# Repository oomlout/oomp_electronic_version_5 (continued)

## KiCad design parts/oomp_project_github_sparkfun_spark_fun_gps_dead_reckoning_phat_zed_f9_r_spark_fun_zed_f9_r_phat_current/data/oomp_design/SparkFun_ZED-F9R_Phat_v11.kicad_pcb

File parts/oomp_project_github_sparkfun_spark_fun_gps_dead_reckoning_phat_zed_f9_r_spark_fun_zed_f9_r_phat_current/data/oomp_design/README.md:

# OOMP KiCad design copy

Open `SparkFun_ZED-F9R_Phat_v11.kicad_pro` (or the `.kicad_pcb` / `.kicad_sch`) in KiCad. Local OOMP libraries are under `libraries/`. Original inputs are preserved in [../original/](../original/).

Only verified unchanged installed KiCad defaults were renamed. Modified, custom, unmatched and unavailable items remain unchanged. Soldering variants are never swapped during conversion. Existing pad coordinates, nets and UUIDs are preserved.

See [conversion_report.yaml](conversion_report.yaml) for every conversion and skip. Copy this directory before editing; regeneration refuses to overwrite edited design files.

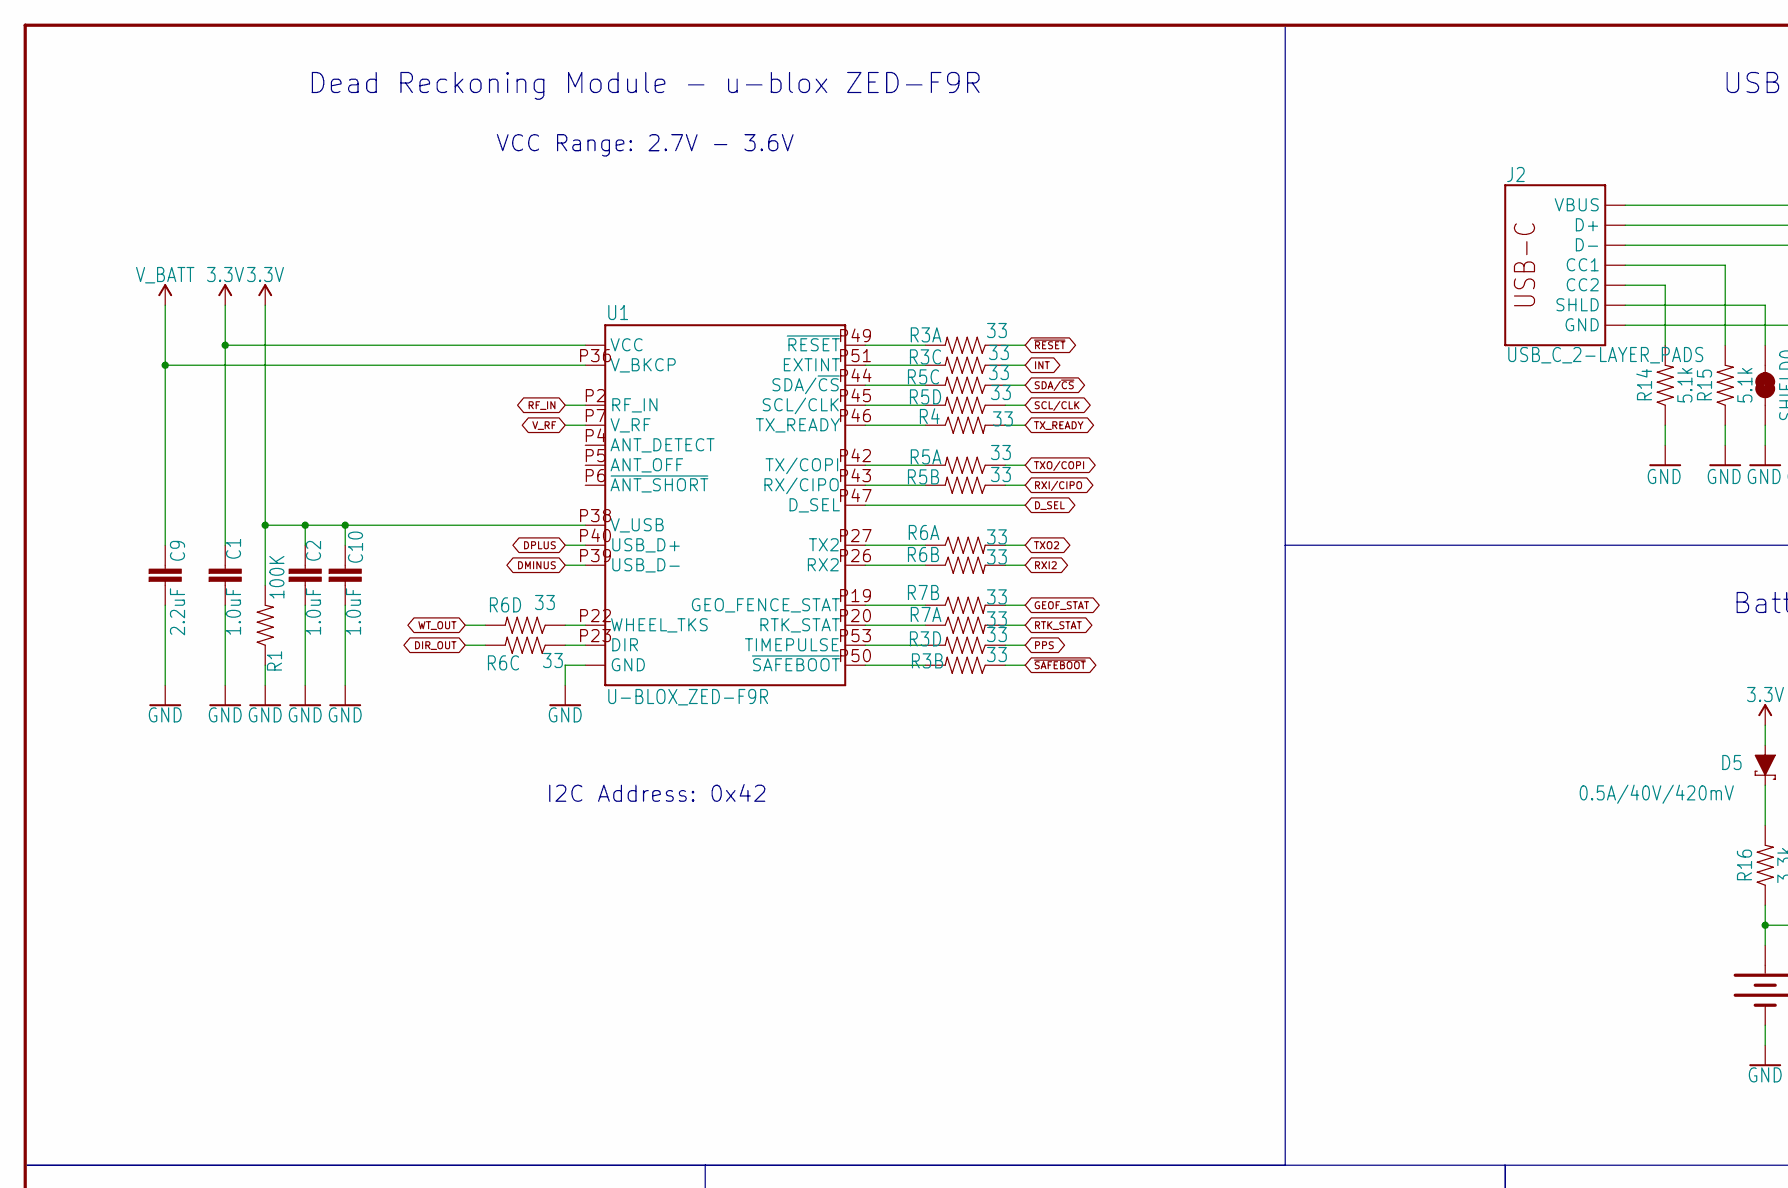
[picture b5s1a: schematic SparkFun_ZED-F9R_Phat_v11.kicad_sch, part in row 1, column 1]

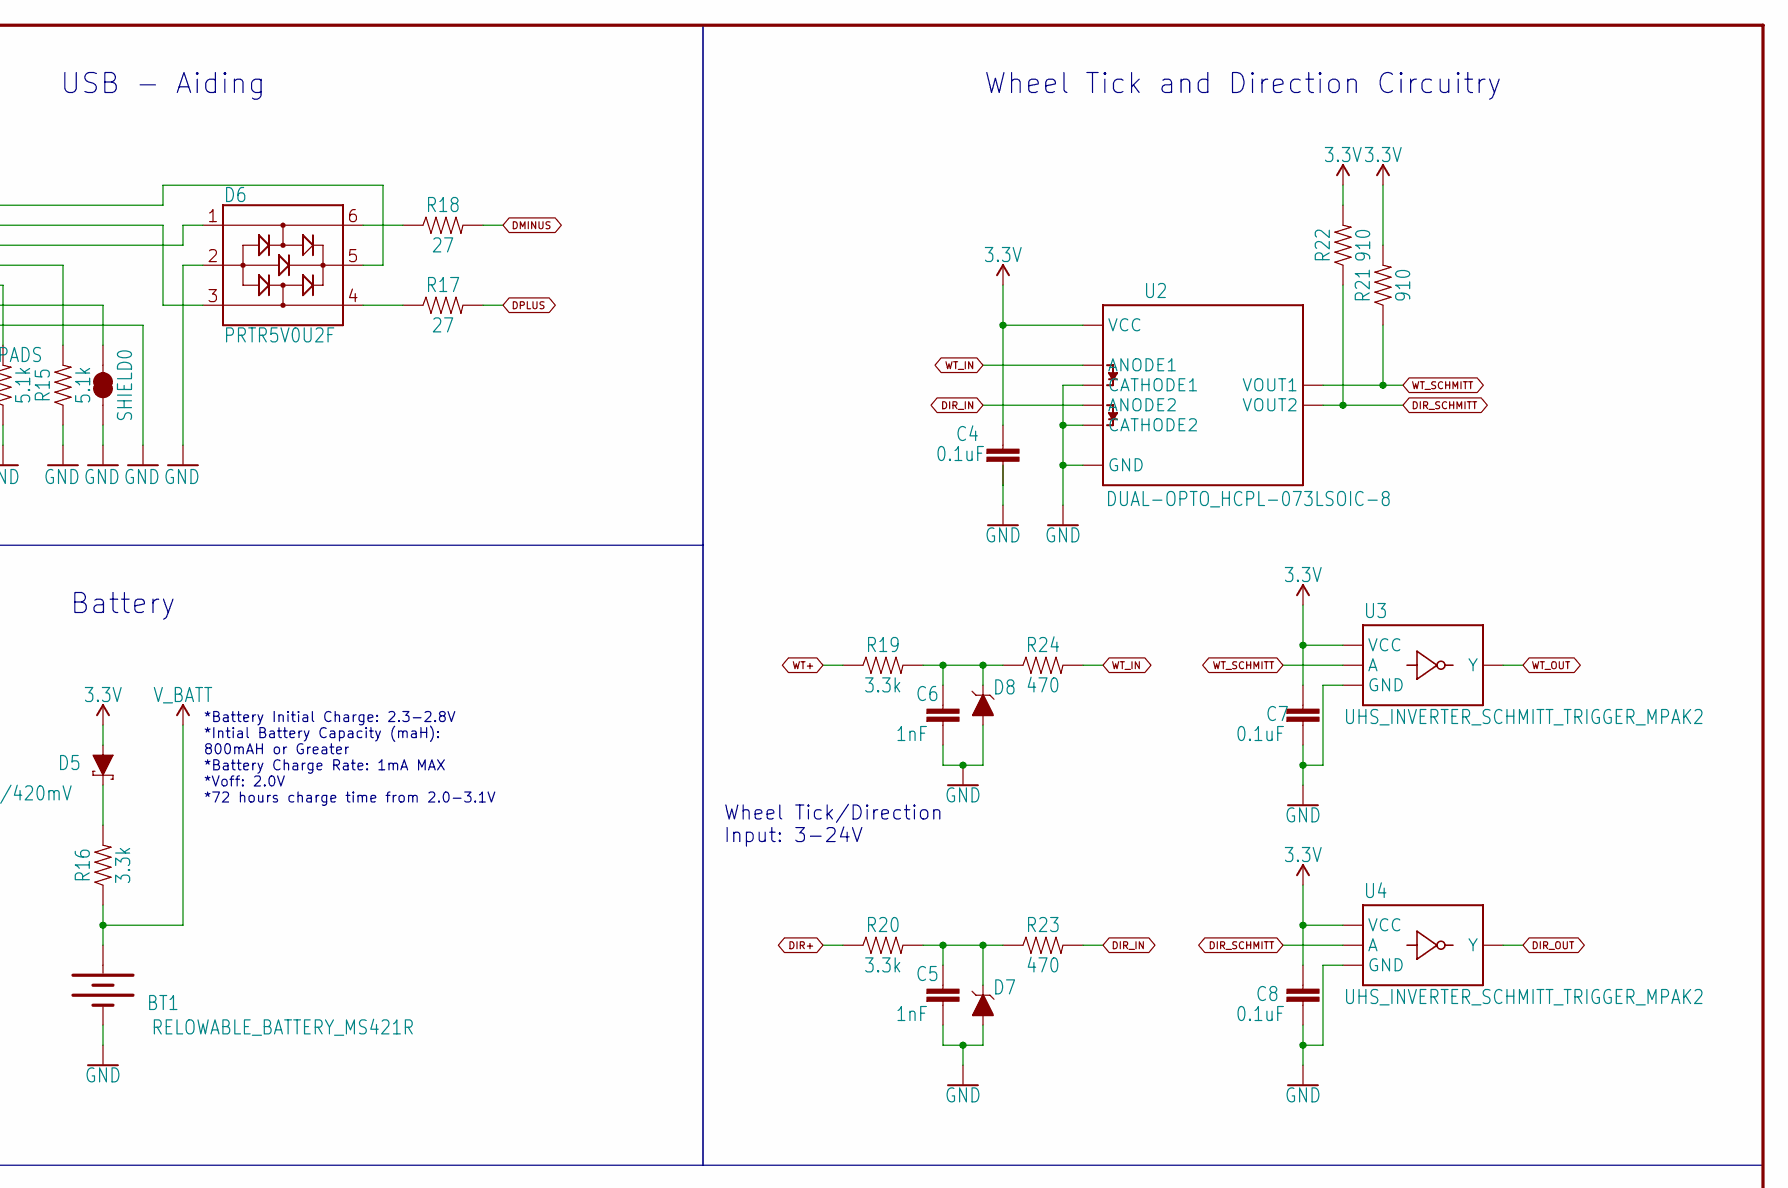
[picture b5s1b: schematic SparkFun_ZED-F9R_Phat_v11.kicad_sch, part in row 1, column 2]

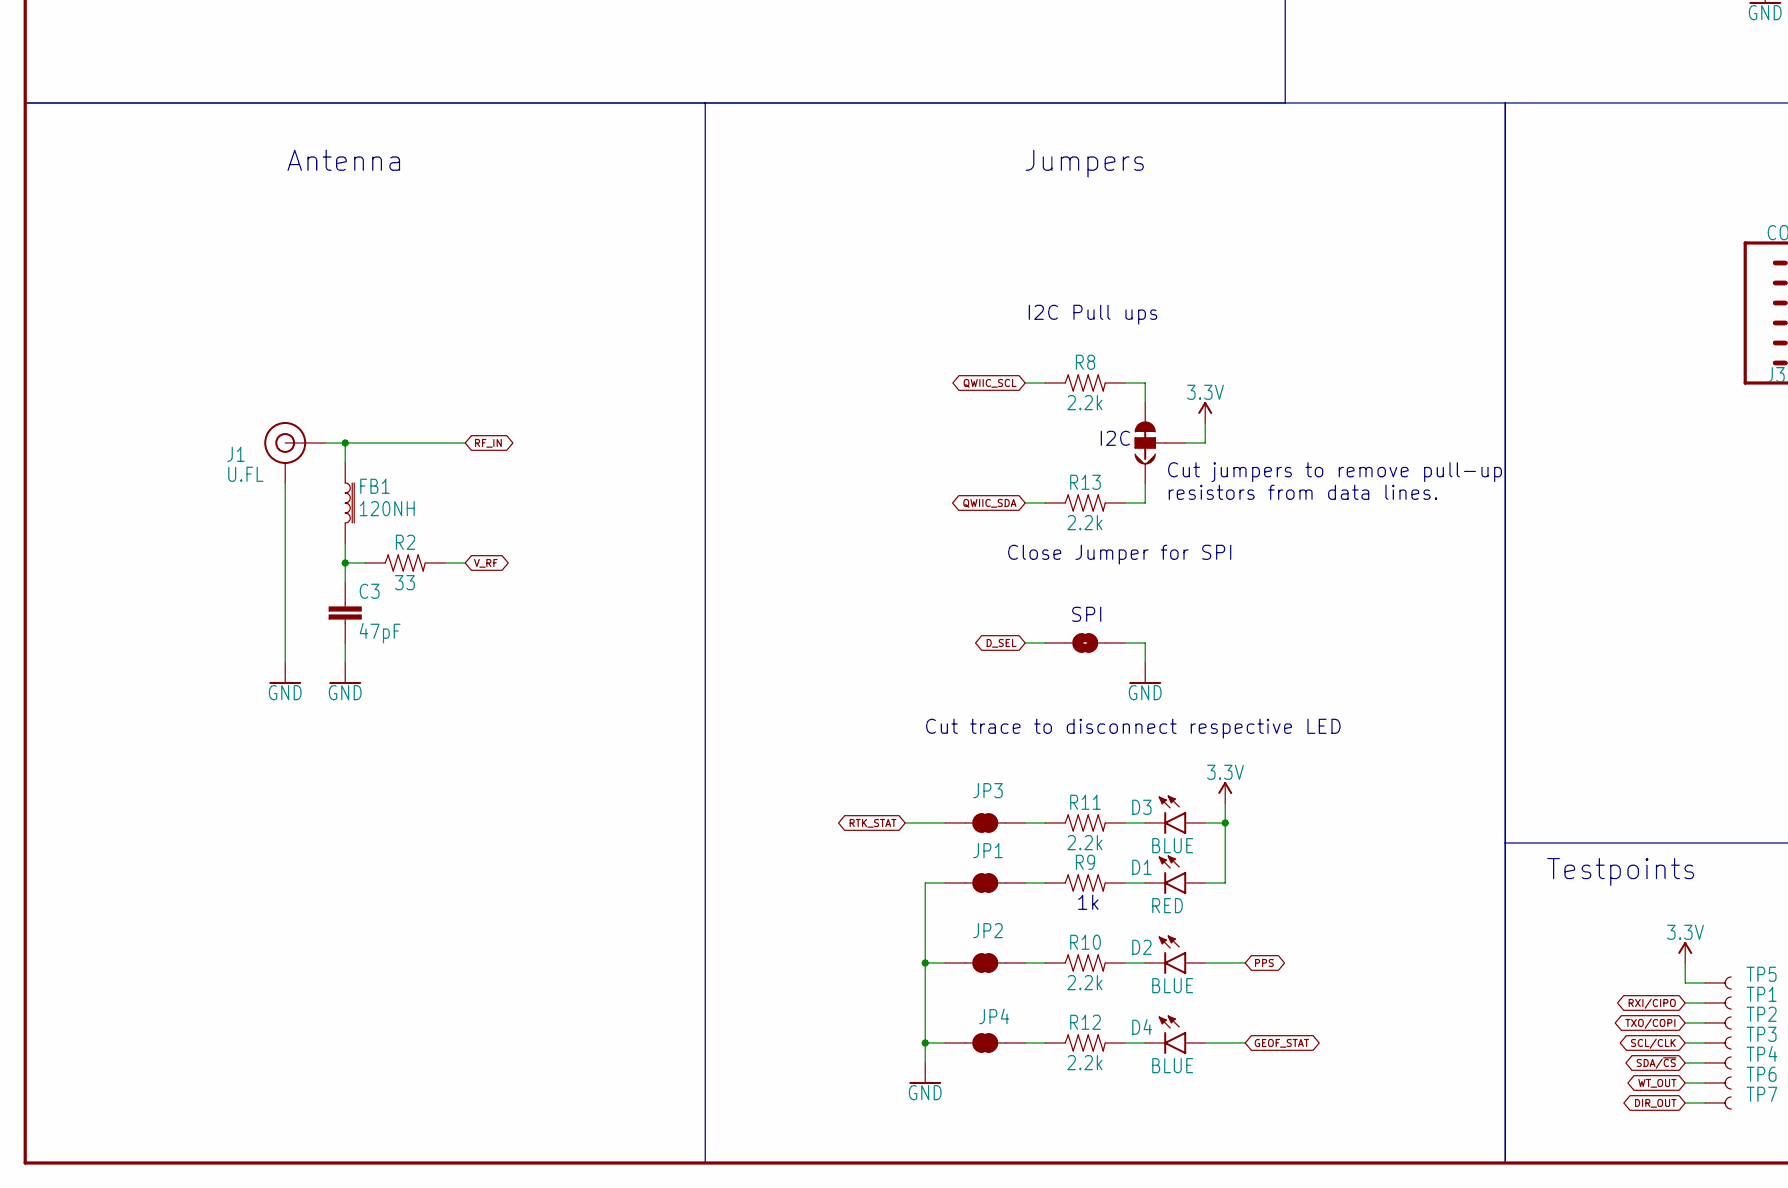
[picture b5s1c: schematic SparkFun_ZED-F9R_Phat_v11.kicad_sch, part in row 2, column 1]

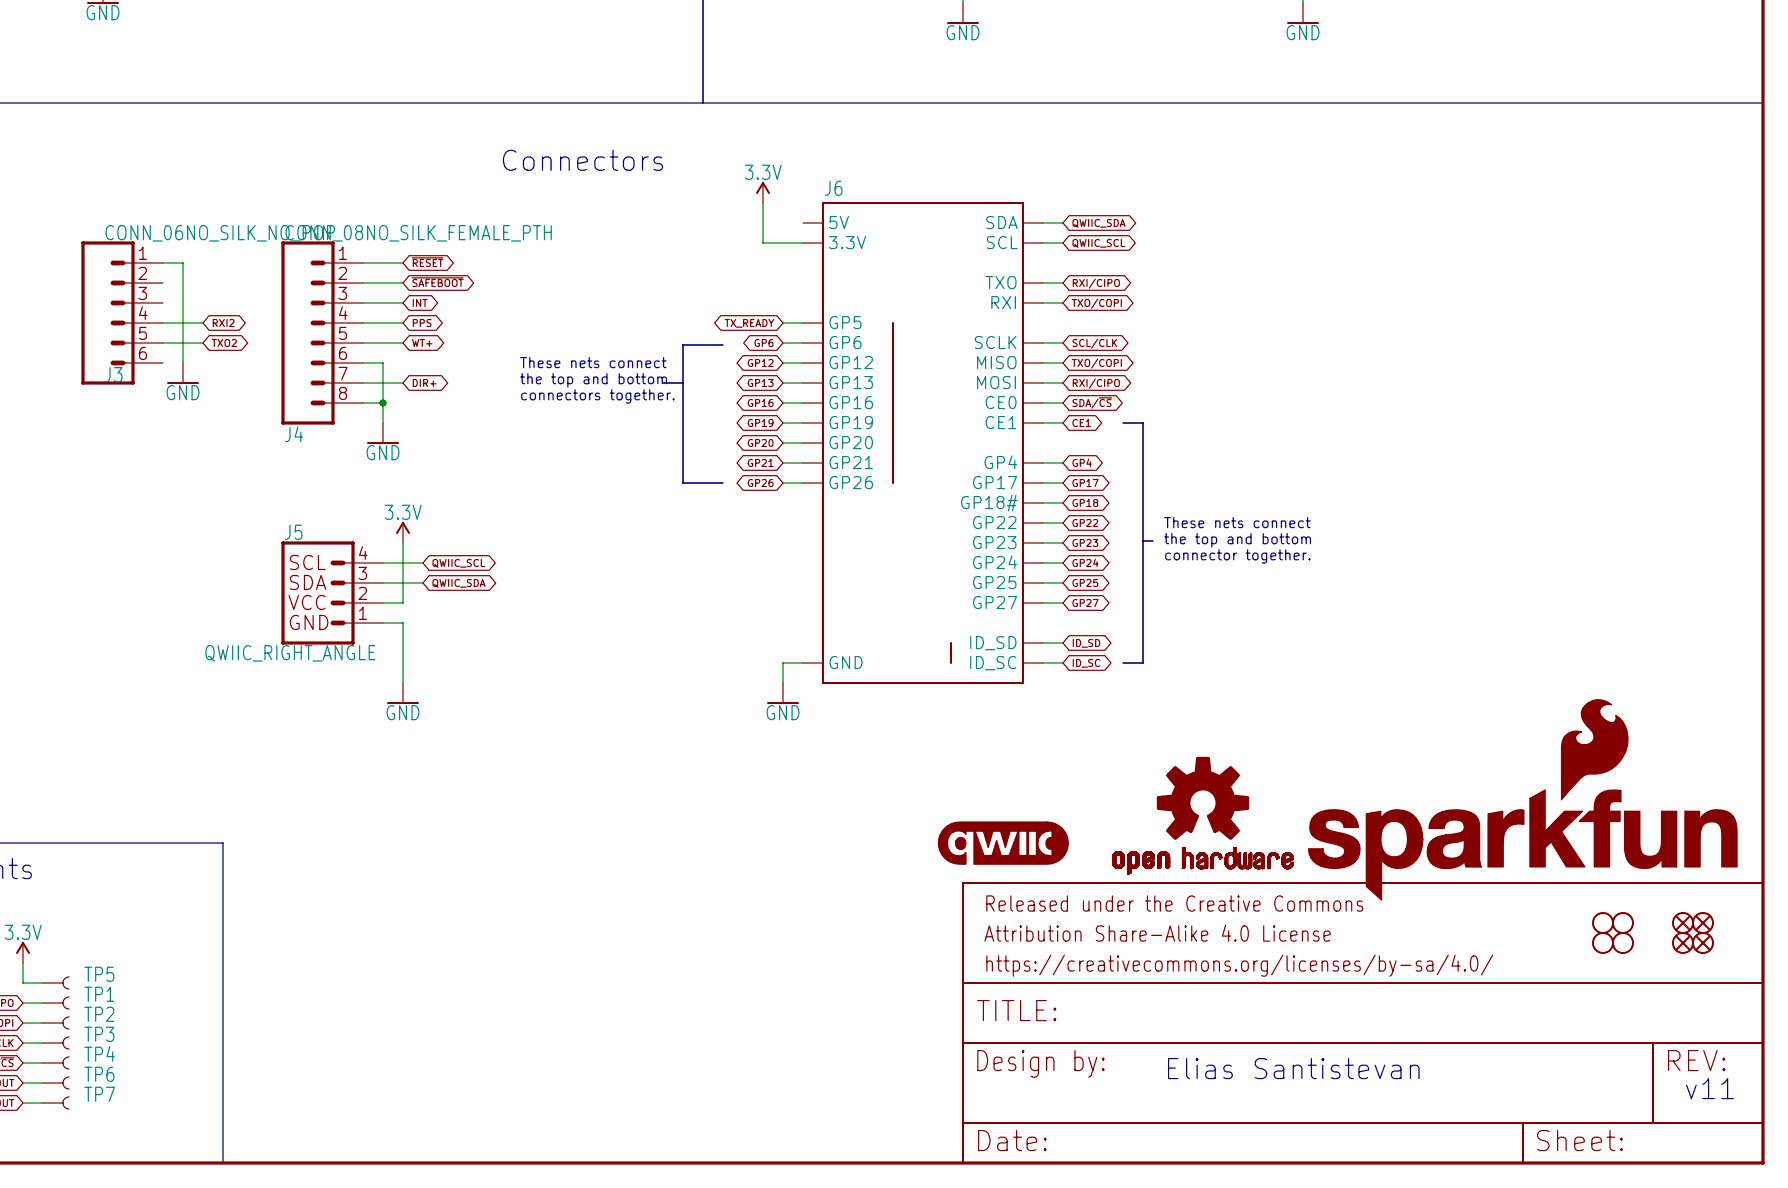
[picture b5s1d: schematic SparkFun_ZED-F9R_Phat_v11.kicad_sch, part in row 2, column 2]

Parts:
BT1: RELOWABLE_BATTERY_MS421R; MS421R_IV03E
C1, C2, C10: 1.0uF; 0402
C3: 47pF; 0402
C4, C7, C8: 0.1uF; 0402
C5, C6: 1nF; 0402
C9: 2.2uF; 0402-TIGHT
D1: RED; LED-0603
D2, D3, D4: BLUE; LED-0603
D5: 0.5A/40V/420mV; SOD-323
D6: PRTR5V0U2F; SOT886
D7, D8: 15V; SOT23-3
FB1: 120NH; 0402_MURATA
FD1, FD2, FD3, FD4: FIDUCIALUFIDUCIAL; FIDUCIAL-MICRO
FRAME1: FRAME-LEDGER; CREATIVE_COMMONS
H1, H2, H3, H4: STAND-OFFTIGHT; STAND-OFF-TIGHT
J1: U.FL
J2: USB_C_2-LAYER_PADS; USB-C-16P-2LAYER-PADS
J3: CONN_06NO_SILK_NO_POP; 1X06_NO_SILK
J4: CONN_08NO_SILK_FEMALE_PTH; 1X08_NO_SILK
J5: QWIIC_RIGHT_ANGLE; JST04_1MM_RA
J6: RASPBERRYPI-40-PIN-GPIO_SMD_STACK_NOHOLES_NOREF; RASPBERRY_PI_HAT_40_PIN_SMD_STACKABLE_NOHOLES_NOREF
JP1, JP2, JP3, JP4: JUMPER-SMT_2_NC_TRACE_SILK; SMT-JUMPER_2_NC_TRACE_SILK
JP5: JUMPER-SMT_2_NO_SILK; SMT-JUMPER_2_NO_SILK
JP6: JUMPER-SMT_3_2-NC_TRACE_SILK; SMT-JUMPER_3_2-NC_TRACE_SILK
LOGO1: QWIIC_LOGO_5MM; QWIIC_5MM
LOGO2: OSHW-LOGOM; OSHW-LOGO-M
LOGO3: SFE_LOGO_NAME_FLAME.2_INCH; SFE_LOGO_NAME_FLAME_.2
R1: 100K; 0402
R2, R4: 33; 0603
R3, R5, R6, R7: 33; 1206_RA
R8, R10, R11, R12, R13: 2.2k; 0603
R9: 1k; 0603
R14, R15: 5.1k; 0402
R16, R19, R20: 3.3k; 0603
R17, R18: 27; 0603
R21, R22: 910; 0603
R23, R24: 470; 0603
SHIELD0: JUMPER-SMT_2_NC_TRACE_SILK; SMT-JUMPER_2_NC_TRACE_SILK
TP1, TP2, TP3, TP4, TP5, TP6, TP7: TEST-POINT3X4; PAD.03X.04
U1: U-BLOX_ZED-F9R; UBLOX_ZED_F9R
U2: DUAL-OPTO_HCPL-073LSOIC-8; SO08
U3, U4: UHS_INVERTER_SCHMITT_TRIGGER_MPAK2; SIP6_MICROPAK2

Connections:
3.3V: C1.1, C2.1, C4.1, C7.1, C8.1, C10.1, D1.A, D3.A, D5.A, J5.2, J6.1 (3.3V), J6.1B (3.3V), J6.17 (3.3V), J6.17B (3.3V), JP6.2, R1.2, R21.2, R22.2, TP5.P$1, U1.P33 (VCC), U1.P34 (VCC), U1.P38 (V_USB), U2.8 (VCC), U3.P6 (VCC), U4.P6 (VCC)
5V: J6.2 (5V), J6.2B (5V), J6.4 (5V), J6.4B (5V)
CE1: J6.26 (CE1), J6.26B (CE1)
DIR+: J4.7, R20.1
DIR_IN: R23.2, U2.4 (ANODE2)
DIR_OUT: R6.P6 (2), TP7.P$1, U4.P4 (Y)
DIR_SCHMITT: R22.1, U2.6 (VOUT2), U4.P2 (A)
DMINUS: R18.2, U1.P39 (USB_D-)
DPLUS: R17.2, U1.P40 (USB_D+)
D_SEL: JP5.1, U1.P47 (D_SEL)
GEOF_STAT: D4.A, R7.P7 (2)
GND: BT1.-, C1.2, C2.2, C3.2, C4.2, C5.2, C6.2, C7.2, C8.2, C9.2, C10.2, D6.2, D7.1 (A), D8.1 (A), J1.1 (GND), J1.2 (GND), J2.GND, J2.GND2 (GND), J3.1, J4.6, J4.8, J5.1, J6.6 (GND), J6.6B (GND), J6.9 (GND), J6.9B (GND), J6.14 (GND), J6.14B (GND), J6.20 (GND), J6.20B (GND), J6.25 (GND), J6.25B (GND), J6.30 (GND), J6.30B (GND), J6.34 (GND), J6.34B (GND), J6.39 (GND), J6.39B (GND), JP1.1, JP2.1, JP4.1, JP5.2, R1.1, R14.1, R15.1, SHIELD0.1, U1.G1 (GND), U1.G2 (GND), U1.G3 (GND), U1.G4 (GND), U1.G5 (GND), U1.G6 (GND), U1.G7 (GND), U1.G8 (GND), U1.G9 (GND), U1.G10 (GND), U1.G11 (GND), U1.G12 (GND), U1.G13 (GND), U1.G14 (GND), U1.G15 (GND), U1.G16 (GND), U1.G17 (GND), U1.G18 (GND), U1.G19 (GND), U1.G20 (GND), U1.G21 (GND), U1.G22 (GND), U1.G23 (GND), U1.G24 (GND), U1.G25 (GND), U1.G26 (GND), U1.G27 (GND), U1.G28 (GND), U1.G29 (GND), U1.G30 (GND), U1.G31 (GND), U1.G32 (GND), U1.G33 (GND), U1.G34 (GND), U1.G35 (GND), U1.G36 (GND), U1.G37 (GND), U1.G38 (GND), U1.G39 (GND), U1.G40 (GND), U1.G41 (GND), U1.G42 (GND), U1.G43 (GND), U1.G44 (GND), U1.G45 (GND), U1.G46 (GND), U1.G47 (GND), U1.G48 (GND), U1.P1 (GND), U1.P3 (GND), U1.P12 (GND), U1.P14 (GND), U1.P32 (GND), U1.P37 (GND), U1.P41 (GND), U1.P48 (GND), U2.2 (CATHODE1), U2.3 (CATHODE2), U2.5 (GND), U3.P3 (GND), U4.P3 (GND)
GP4: J6.7 (GP4), J6.7B (GP4)
GP6: J6.31 (GP6), J6.31B (GP6)
GP12: J6.32 (GP12), J6.32B (GP12)
GP13: J6.33 (GP13), J6.33B (GP13)
GP16: J6.36 (GP16), J6.36B (GP16)
GP17: J6.11 (GP17), J6.11B (GP17)
GP18: J6.12 (GP18#), J6.12B (GP18#)
GP19: J6.35 (GP19), J6.35B (GP19)
GP20: J6.38 (GP20), J6.38B (GP20)
GP21: J6.40 (GP21), J6.40B (GP21)
GP22: J6.15 (GP22), J6.15B (GP22)
GP23: J6.16 (GP23), J6.16B (GP23)
GP24: J6.18 (GP24), J6.18B (GP24)
GP25: J6.22 (GP25), J6.22B (GP25)
GP26: J6.37 (GP26), J6.37B (GP26)
GP27: J6.13 (GP27), J6.13B (GP27)
ID_SC: J6.28 (ID_SC), J6.28B (ID_SC)
ID_SD: J6.27 (ID_SD), J6.27B (ID_SD)
INT: J4.3, R3.P3 (1)
unnamed: JP6.1, R13.2
unnamed: D5.C, R16.2
unnamed: JP6.3, R8.2
unnamed: D1.C, R9.2
unnamed: C3.1, FB1.P2 (2), R2.1
unnamed: D6.6, R18.1
unnamed: D6.4, R17.1
unnamed: JP1.2, R9.1
unnamed: D6.3, J2.A6 (D+), J2.B6 (D+)
unnamed: D6.5, J2.VBUS1 (VBUS), J2.VBUS2 (VBUS)
unnamed: D6.1, J2.A7 (D-), J2.B7 (D-)
unnamed: J2.B5 (CC2), R14.2
unnamed: R3.P8 (2), U1.P49 (~RESET)
unnamed: R3.P6 (2), U1.P51 (EXTINT)
unnamed: R5.P6 (2), U1.P44 (SDA/~CS)
unnamed: JP4.2, R12.1
unnamed: D4.C, R12.2
unnamed: J2.A5 (CC1), R15.2
unnamed: R5.P5 (2), U1.P45 (SCL/CLK)
unnamed: R4.1, U1.P46 (TX_READY)
unnamed: R5.P8 (2), U1.P42 (TX/COPI)
unnamed: JP3.2, R11.1
unnamed: JP2.2, R10.1
unnamed: D2.C, R10.2
unnamed: D3.C, R11.2
unnamed: R5.P7 (2), U1.P43 (RX/CIPO)
unnamed: C6.1, D8.3 (C), R19.2, R24.1
unnamed: R7.P2 (1), U1.P19 (GEO_FENCE_STAT)
unnamed: R7.P1 (1), U1.P20 (RTK_STAT)
unnamed: R3.P5 (2), U1.P53 (TIMEPULSE)
unnamed: R3.P7 (2), U1.P50 (~SAFEBOOT)
unnamed: R6.P1 (1), U1.P27 (TX2)
unnamed: R6.P2 (1), U1.P26 (RX2)
unnamed: R6.P4 (1), U1.P22 (WHEEL_TKS)
unnamed: R6.P3 (1), U1.P23 (DIR)
unnamed: C5.1, D7.3 (C), R20.2, R23.1
PPS: D2.A, J4.4, R3.P4 (1)
QWIIC_SCL: J5.4, J6.5 (SCL), J6.5B (SCL), R8.1
QWIIC_SDA: J5.3, J6.3 (SDA), J6.3B (SDA), R13.1
RF_IN: FB1.P1 (1), J1.FEED (SIGNAL), U1.P2 (RF_IN)
RTK_STAT: JP3.1, R7.P8 (2)
RXI2: J3.4, R6.P7 (2)
RXI/CIPO: J6.8 (TXO), J6.8B (TXO), J6.19 (MOSI), J6.19B (MOSI), R5.P2 (1), TP1.P$1
SCL/CLK: J6.23 (SCLK), J6.23B (SCLK), R5.P4 (1), TP3.P$1
SDA/~CS: J6.24 (CE0), J6.24B (CE0), R5.P3 (1), TP4.P$1
SHIELD: J2.SHLD1 (SHLD), J2.SHLD2 (SHLD), J2.SHLD3 (SHLD), J2.SHLD4 (SHLD), SHIELD0.2
TXO2: J3.5, R6.P8 (2)
TXO/COPI: J6.10 (RXI), J6.10B (RXI), J6.21 (MISO), J6.21B (MISO), R5.P1 (1), TP2.P$1
TX_READY: J6.29 (GP5), J6.29B (GP5), R4.2
V_BATT: BT1.+, C9.1, R16.1, U1.P36 (V_BKCP)
V_RF: R2.2, U1.P7 (V_RF)
WT+: J4.5, R19.1
WT_IN: R24.2, U2.1 (ANODE1)
WT_OUT: R6.P5 (2), TP6.P$1, U3.P4 (Y)
WT_SCHMITT: R21.1, U2.7 (VOUT1), U3.P2 (A)
~RESET: J4.1, R3.P1 (1)
~SAFEBOOT: J4.2, R3.P2 (1)

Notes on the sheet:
I2C Pull ups
These nets connect the top and bottom connectors together.
These nets connect the top and bottom connector together.
Wheel Tick and Direction Circuitry
Connectors
USB - Aiding
SPI
Close Jumper for SPI
I2C
Antenna
Dead Reckoning Module - u-blox ZED-F9R
Elias Santistevan
v11
I2C Address: 0x42
Wheel Tick/Direction Input: 3-24V
Testpoints
Cut trace to disconnect respective LED
Battery
Cut jumpers to remove pull-up resistors from data lines.
VCC Range: 2.7V - 3.6V
Jumpers
*Battery Initial Charge: 2.3-2.8V *Intial Battery Capacity (maH): 800mAH or Greater *Battery Charge Rate: 1mA MAX *Voff: 2.0V *72 hours charge time from 2.0-3.1V

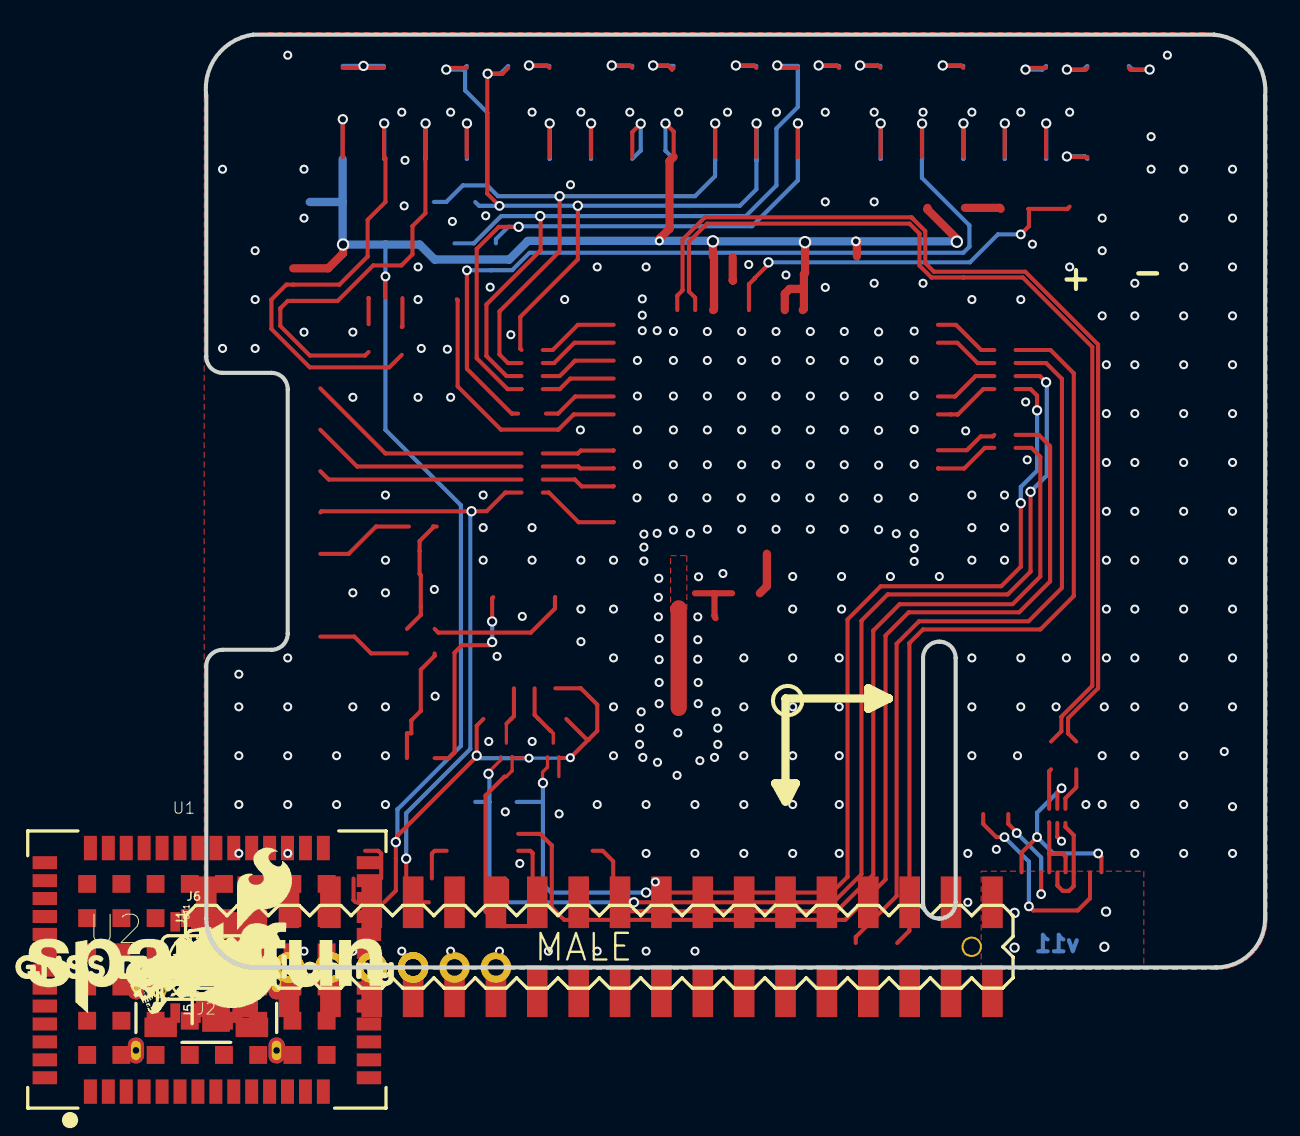
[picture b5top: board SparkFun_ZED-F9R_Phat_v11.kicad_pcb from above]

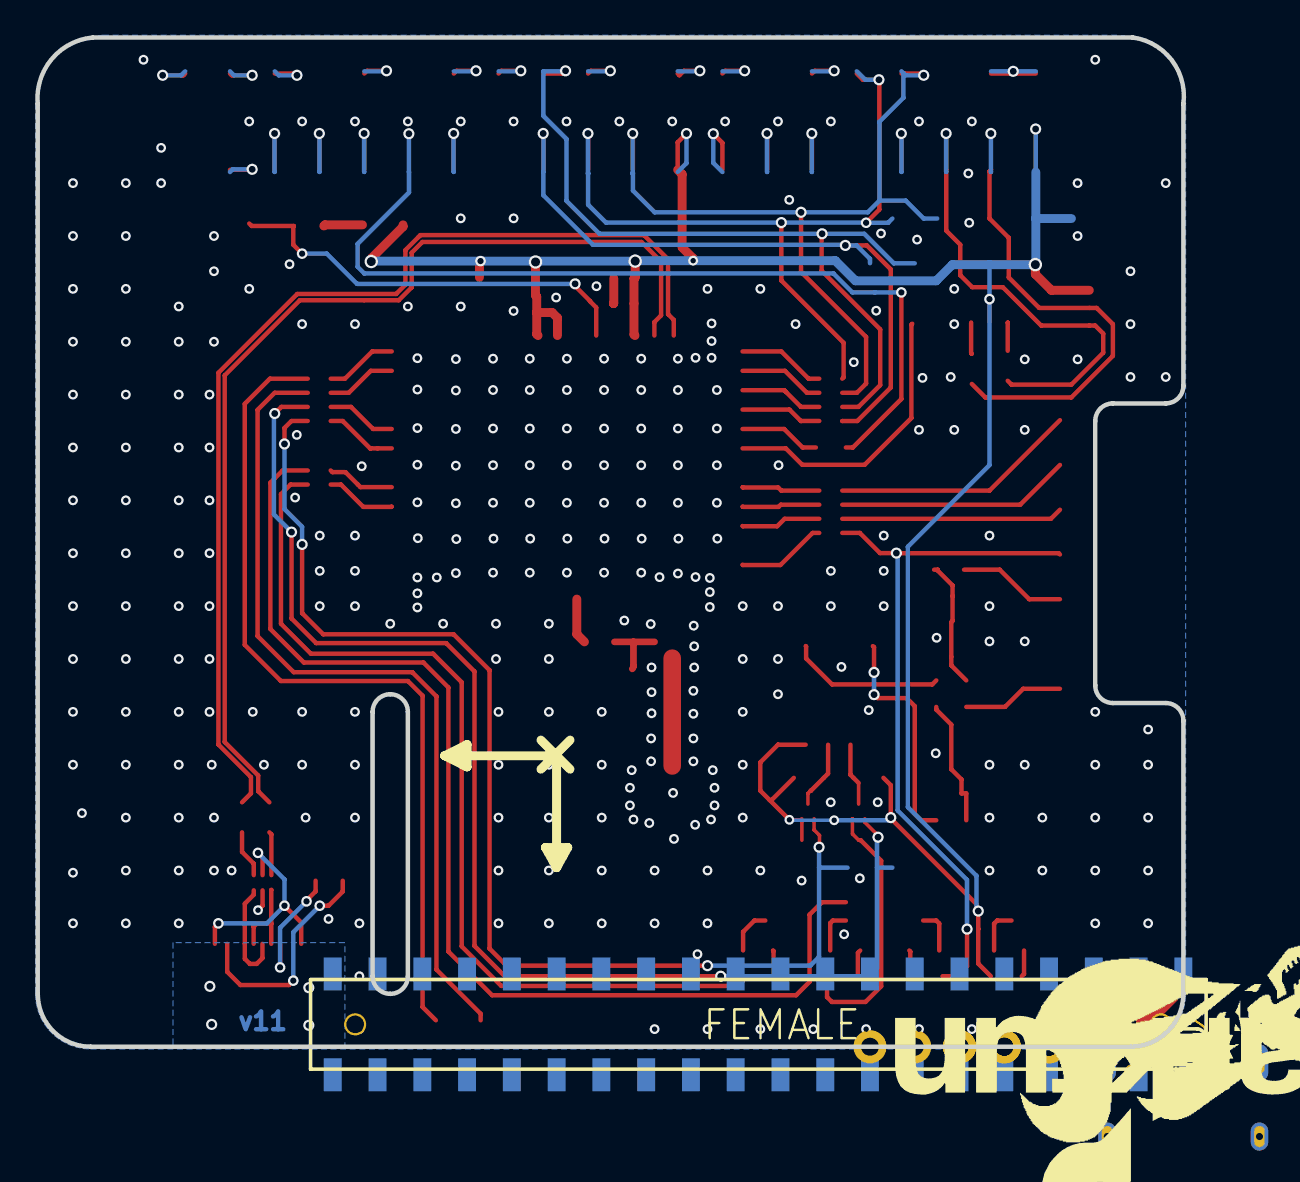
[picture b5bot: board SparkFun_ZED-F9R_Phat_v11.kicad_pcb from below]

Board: 2 copper layers, 65.0 x 57.3 mm, 124 parts (27 on the bottom side), 88 nets.

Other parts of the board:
U$1: ##RST##28
U$2: ##SFBT##30
U$3: PPS9
U$4: PWR7
U$5: GEO11
U$6: #RXI2#34
U$7: #INT#1
U$8: #PPS#3
U$9: SFE_LOGO_NAME_FLAME_.3@1
U$10: #TXO2#235
U$11: #W##2253
U$12: #W##2254
U$13: #D##2249
U$14: GNSS_DEAD_RECKONING25
U$15: #D##2250
U$16: ZED#F9R25
U$17: BLK22
U$18, U$19: #GND#20
U$20: #SPI#4
U$21: L1#L26
U$22: #I2C#5
U$23: RTK13
U$24: GRN23
U$25, U$28: Z20
U$26, U$29: Y19
U$27, U$45: X18
U$31, U$36: DEAD#RECKONING#GPS#BOARD#SILK#FINAL#JPG
U$32: ##RST##27
U$33: ##SFBT##29
U$34: #INT#0
U$35: #PPS#2
U$37: #W##2251
U$38: #W##2252
U$39: #D##2247
U$40: #D##2248
U$41: ANTENNA6
U$42: #TXO2#236
U$43: #RXI2#35
U$44: #SHLD#2258

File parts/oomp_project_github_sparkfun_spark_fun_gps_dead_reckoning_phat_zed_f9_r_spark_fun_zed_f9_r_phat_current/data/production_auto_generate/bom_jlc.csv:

Comment,Designator,Footprint,LCSC Part #
,U$32,SparkFun_ZED-F9R_Phat_v11-import-fps:##RST##27,
,U$1,SparkFun_ZED-F9R_Phat_v11-import-fps:##RST##28,
,U$33,SparkFun_ZED-F9R_Phat_v11-import-fps:##SFBT##29,
,U$2,SparkFun_ZED-F9R_Phat_v11-import-fps:##SFBT##30,
,U$39,SparkFun_ZED-F9R_Phat_v11-import-fps:#D##2247,
,U$40,SparkFun_ZED-F9R_Phat_v11-import-fps:#D##2248,
,U$13,SparkFun_ZED-F9R_Phat_v11-import-fps:#D##2249,
,U$15,SparkFun_ZED-F9R_Phat_v11-import-fps:#D##2250,
,"U$18,U$19",SparkFun_ZED-F9R_Phat_v11-import-fps:#GND#20,
,U$22,SparkFun_ZED-F9R_Phat_v11-import-fps:#I2C#5,
,U$34,SparkFun_ZED-F9R_Phat_v11-import-fps:#INT#0,
,U$7,SparkFun_ZED-F9R_Phat_v11-import-fps:#INT#1,
,U$35,SparkFun_ZED-F9R_Phat_v11-import-fps:#PPS#2,
,U$8,SparkFun_ZED-F9R_Phat_v11-import-fps:#PPS#3,
,U$6,SparkFun_ZED-F9R_Phat_v11-import-fps:#RXI2#34,
,U$43,SparkFun_ZED-F9R_Phat_v11-import-fps:#RXI2#35,
,U$44,SparkFun_ZED-F9R_Phat_v11-import-fps:#SHLD#2258,
,U$20,SparkFun_ZED-F9R_Phat_v11-import-fps:#SPI#4,
,U$10,SparkFun_ZED-F9R_Phat_v11-import-fps:#TXO2#235,
,U$42,SparkFun_ZED-F9R_Phat_v11-import-fps:#TXO2#236,
,U$37,SparkFun_ZED-F9R_Phat_v11-import-fps:#W##2251,
,U$38,SparkFun_ZED-F9R_Phat_v11-import-fps:#W##2252,
,U$11,SparkFun_ZED-F9R_Phat_v11-import-fps:#W##2253,
,U$12,SparkFun_ZED-F9R_Phat_v11-import-fps:#W##2254,
,J3,SparkFun_ZED-F9R_Phat_v11-import-fps:1X06_NO_SILK,C37208
,J4,SparkFun_ZED-F9R_Phat_v11-import-fps:1X08_NO_SILK,C492421
,U$41,SparkFun_ZED-F9R_Phat_v11-import-fps:ANTENNA6,
,U$17,SparkFun_ZED-F9R_Phat_v11-import-fps:BLK22,
,"U$31,U$36",SparkFun_ZED-F9R_Phat_v11-import-fps:DEAD#RECKONING#GPS#BOARD#SILK#FINAL#JPG,
,U$5,SparkFun_ZED-F9R_Phat_v11-import-fps:GEO11,
,U$14,SparkFun_ZED-F9R_Phat_v11-import-fps:GNSS_DEAD_RECKONING25,
,U$24,SparkFun_ZED-F9R_Phat_v11-import-fps:GRN23,
,U$21,SparkFun_ZED-F9R_Phat_v11-import-fps:L1#L26,
,U$3,SparkFun_ZED-F9R_Phat_v11-import-fps:PPS9,
,U$4,SparkFun_ZED-F9R_Phat_v11-import-fps:PWR7,
,U$23,SparkFun_ZED-F9R_Phat_v11-import-fps:RTK13,
,U$9,SparkFun_ZED-F9R_Phat_v11-import-fps:SFE_LOGO_NAME_FLAME_.3@1,
,J2,SparkFun_ZED-F9R_Phat_v11-import-fps:USB-C-16P-2LAYER-PADS,
,"U$27,U$45",SparkFun_ZED-F9R_Phat_v11-import-fps:X18,
,"U$26,U$29",SparkFun_ZED-F9R_Phat_v11-import-fps:Y19,
,"U$25,U$28",SparkFun_ZED-F9R_Phat_v11-import-fps:Z20,
,U$16,SparkFun_ZED-F9R_Phat_v11-import-fps:ZED#F9R25,
0.1uF,"C4,C7,C8",SparkFun_ZED-F9R_Phat_v11-import-fps:0402,C60474
0.5A/40V/420mV,D5,SparkFun_ZED-F9R_Phat_v11-import-fps:SOD-323,
1.0uF,"C1,C2,C10",SparkFun_ZED-F9R_Phat_v11-import-fps:0402,C2887021
100K,R1,SparkFun_ZED-F9R_Phat_v11-import-fps:0402,C25530
120NH,FB1,SparkFun_ZED-F9R_Phat_v11-import-fps:0402_MURATA,
15V,"D7,D8",SparkFun_ZED-F9R_Phat_v11-import-fps:SOT23-3,
1k,R9,SparkFun_ZED-F9R_Phat_v11-import-fps:0603,C2907002
1nF,"C5,C6",SparkFun_ZED-F9R_Phat_v11-import-fps:0402,
2.2k,"R8,R10,R11,R12,R13",SparkFun_ZED-F9R_Phat_v11-import-fps:0603,C4190
2.2uF,C9,SparkFun_ZED-F9R_Phat_v11-import-fps:0402-TIGHT,C12530
27,"R17,R18",SparkFun_ZED-F9R_Phat_v11-import-fps:0603,C25190
3.3k,"R16,R19,R20",SparkFun_ZED-F9R_Phat_v11-import-fps:0603,C22978
33,"R2,R4",SparkFun_ZED-F9R_Phat_v11-import-fps:0603,C23140
33,"R3,R5,R6,R7",SparkFun_ZED-F9R_Phat_v11-import-fps:1206_RA,C2907384
470,"R23,R24",SparkFun_ZED-F9R_Phat_v11-import-fps:0603,C23179
47pF,C3,SparkFun_ZED-F9R_Phat_v11-import-fps:0402,
5.1k,"R14,R15",SparkFun_ZED-F9R_Phat_v11-import-fps:0402,C25905
910,"R21,R22",SparkFun_ZED-F9R_Phat_v11-import-fps:0603,
BLUE,"D2,D3,D4",SparkFun_ZED-F9R_Phat_v11-import-fps:LED-0603,
DUAL-OPTO_HCPL-073LSOIC-8,U2,SparkFun_ZED-F9R_Phat_v11-import-fps:SO08,
FIDUCIALUFIDUCIAL,"FD1,FD2,FD3,FD4",SparkFun_ZED-F9R_Phat_v11-import-fps:FIDUCIAL-MICRO,
FRAME-LEDGER,FRAME1,SparkFun_ZED-F9R_Phat_v11-import-fps:CREATIVE_COMMONS,
JUMPER-SMT_2_NC_TRACE_SILK,"JP1,JP2,JP3,JP4,SHIELD0",SparkFun_ZED-F9R_Phat_v11-import-fps:SMT-JUMPER_2_NC_TRACE_SILK,
JUMPER-SMT_2_NO_SILK,JP5,SparkFun_ZED-F9R_Phat_v11-import-fps:SMT-JUMPER_2_NO_SILK,
JUMPER-SMT_3_2-NC_TRACE_SILK,JP6,SparkFun_ZED-F9R_Phat_v11-import-fps:SMT-JUMPER_3_2-NC_TRACE_SILK,
PRTR5V0U2F,D6,SparkFun_ZED-F9R_Phat_v11-import-fps:SOT886,
QWIIC_RIGHT_ANGLE,J5,SparkFun_ZED-F9R_Phat_v11-import-fps:JST04_1MM_RA,
RASPBERRYPI-40-PIN-GPIO_SMD_STACK_NOHOLES_NOREF,J6,SparkFun_ZED-F9R_Phat_v11-import-fps:RASPBERRY_PI_HAT_40_PIN_SMD_STACKABLE_NOHOLES_NOREF,
RED,D1,SparkFun_ZED-F9R_Phat_v11-import-fps:LED-0603,
RELOWABLE_BATTERY_MS421R,BT1,SparkFun_ZED-F9R_Phat_v11-import-fps:MS421R_IV03E,
TEST-POINT3X4,"TP1,TP2,TP3,TP4,TP5,TP6,TP7",SparkFun_ZED-F9R_Phat_v11-import-fps:PAD.03X.04,
U-BLOX_ZED-F9R,U1,SparkFun_ZED-F9R_Phat_v11-import-fps:UBLOX_ZED_F9R,
U.FL,J1,SparkFun_ZED-F9R_Phat_v11-import-fps:U.FL,
UHS_INVERTER_SCHMITT_TRIGGER_MPAK2,"U3,U4",SparkFun_ZED-F9R_Phat_v11-import-fps:SIP6_MICROPAK2,
